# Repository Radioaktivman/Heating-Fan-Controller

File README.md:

# Heating Fan Controller

A temperature-controlled fan system for improving radiator efficiency through forced convection.

## Overview

This project provides an automated control system for heating radiator fans. By using forced convection, it significantly improves the heat output and efficiency of traditional radiators, especially at lower flow temperatures. This is particularly beneficial for heat pump systems that operate more efficiently at lower temperatures.

## Features

- **Temperature-Based Control**: Automatically activates fans based on radiator temperature
- **PWM Fan Control**: Smooth and quiet fan speed regulation
- **Efficient Heat Distribution**: Improves radiator efficiency and room heating
- **Low Noise Operation**: Designed for quiet residential use

## Why Use Radiator Fans?

Classical radiators typically require high flow temperatures to effectively heat a room. Adding forced convection with PC fans can:

- Significantly enhance radiator efficiency at low flow temperatures
- Enable heat pumps to operate at optimal (lower) temperatures
- Reduce heating costs while maintaining comfort
- Improve heat distribution in the room

### Advanced Monitoring and Control

With four temperature sensors, this controller provides comprehensive monitoring of the entire heating cycle:

- **Flow/Return Temperature Monitoring**: Track the temperature difference across the radiator to measure heat transfer efficiency
- **Air Temperature Delta**: Measure the temperature increase from inlet (bottom) to outlet (top) to quantify the actual heating effect
- **Performance Optimization**: Automatically adjust fan speed based on the temperature differentials to maximize efficiency
- **System Diagnostics**: Identify issues like poor circulation, air locks, or insufficient flow temperatures
- **Energy Efficiency**: Calculate the actual heat output and optimize fan operation to minimize electricity consumption while maximizing heat distribution

## Hardware Components

### Required Components
- **ESP Heating Controller PCB** (Rev 1.0 - design files in `/PCB` folder)
  - PCBs available from maintainer (contact via PM)
  - [3D-printable housing available on Thingiverse](https://www.thingiverse.com/thing:7254499)
- Temperature sensors: DS18B20 (up to 4 sensors supported)
- **12V PC fans** - Both 3-pin and 4-pin fans  up to 6 fans total
  - 3-pin fans: Standard DC voltage control
  - 4-pin PWM fans: Precise PWM speed control (recommended for quieter operation)
  - Note: All fans operate at the same speed (shared PWM signal)
- 12V power supply 
- **[3D-printed mounting clips](https://www.thingiverse.com/thing:5943925)** for attaching fans to radiators 

### Recommended Fans
High-quality PC fans operating at low speeds (<500 RPM) are essentially inaudible while providing significant heat output improvement. The controller supports both 3-pin and 4-pin fans.

## PCB Design

*ESP Heating Controller Rev 1.0 by 2SimpleEnergy GmbH*

The `/PCB` folder contains the custom PCB design files for this project. 

### Hardware Specifications

**Microcontroller:**
- ESP32-WROOM module (WiFi/Bluetooth enabled)
- Enables smart home integration and remote monitoring

**Fan Outputs:**
- **6 fan output channels** (F1-F6)
- **All channels share the same PWM control signal** - fans operate synchronously at the same speed
- Supports multiple fans or fan groups connected across the 6 outputs
- **Compatible with both 3-pin and 4-pin PC fans:**
  - **3-pin fans**: Standard DC voltage control (full voltage = full speed)
  - **4-pin PWM fans**: Advanced PWM control with tachometer feedback for precise speed regulation and RPM monitoring
- Standard 4-pin fan connectors for easy plug-and-play installation

**Temperature Sensor Inputs:**
- **3 Pin Connector ** (S1-S4) for DS18B20 or similar sensors
- Designed for comprehensive heating system monitoring:
  - **Flow temperature**: Monitor water entering the radiator
  - **Return flow temperature**: Monitor water leaving the radiator
  - **Air inlet temperature**: Measure air temperature at bottom of radiator (before heating)
  - **Air outlet temperature**: Measure air temperature at top of radiator (after heating)
- Pull-up resistors (R1, R3, R5, R7) integrated on board
- Enables precise control based on actual radiator performance and efficiency calculations

**User Interface:**
- 3 tactile buttons (SW1, SW2, SW3) for manual control and configuration
- Status LED indicators

**Power Supply:**
- DC barrel jack connector (DC0) for 12V input
- Onboard voltage regulation for ESP32 (3.3V)

**PCB Housing:**
A 3D-printable housing for this PCB is available on Thingiverse for protection and professional mounting:
👉 **[ESP Heating Controller PCB Housing](https://www.thingiverse.com/thing:7254499)**

**PCB Availability:**
I have some leftover PCBs ! If you're interested in procuring a board instead of manufacturing it yourself, please contact me via private message on GitHub.

## Installation

### Hardware Setup

1. **3D-print the components**:
   - Download and print the **[PCB housing](https://www.thingiverse.com/thing:7254499)** for the controller
   - Download and print the **[fan mounting clips](https://www.thingiverse.com/thing:5943925)** (2 clips per fan)
2. **Assemble the controller**:
   - Install the ESP Heating Controller PCB into the housing
   - Mount the housing to wall or heating
3. **Prepare the fans**: Mount the PC fans using the printed clips below your radiators
   - Insert clips from below between the radiator ribs
   - Ensure secure fit (designed for 75mm inner distance, adjustable)
   - Use cable ties through the eyelets for cable management
3. **Wire the temperature sensor**: Connect DS18B20 to the controller
   - Red: +3.3V 
   - Yellow/Data: Data line (with 4.7kΩ pull-up resistor)
   - Black: GND
3. **Connect the fans**: Wire fans to the controller output
4. **Power supply**: Connect 12V power supply

### Software Setup

1. Clone this repository:
```bash
git clone https://github.com/Radioaktivman/Heating-Fan-Controller.git
cd Heating-Fan-Controller
```

2. **Firmware Option: Tasmota**

This controller uses Tasmota firmware for easy configuration and smart home integration.

**Step-by-Step Tasmota Configuration:**

**Step 1: Flash Tasmota Firmware**
1. Flash Tasmota firmware to the ESP32 module using your preferred method (web flasher, esptool, etc.)
2. Select ESP32 variant during flashing

**Step 2: Initial WiFi Setup**
1. Power on the device - it will create a WiFi access point named "tasmota-XXXXXX"
2. Connect to this access point with your phone/computer
3. Configure your WiFi credentials:
   - SSID: YourNetworkName
   - Password: [Your WiFi Password]
4. The device will restart and connect to your network

**Step 3: Access Tasmota Web Interface**
1. Find the device's IP address (check your router or use Tasmota discovery)
2. Open a web browser and navigate to the IP address
3. You should see the Tasmota web interface

**Step 4: Configure Module Type**
1. Go to **Configuration** → **Configure Module**
2. Set **Module type** to **ESP32S3 (1)**
3. Click **Save** - the device will restart

**Step 5: Configure GPIO Pins**
After restart, go back to **Configuration** → **Configure Module** and set the following GPIO pins:

| GPIO Pin | Function | Number |
|----------|----------|--------|
| GPIO03 | DS18x20 | 4 |
| GPIO04 | Button | 1 |
| GPIO05 | Button | 2 |
| GPIO06 | Button | 3 |
| GPIO11 | DS18x20 | 3 |
| GPIO14 | DS18x20 | 2 |
| GPIO16 | Relay_i | 1 |
| GPIO18 | PWM | 1 |
| GPIO48 | DS18x20 | 1 |

Leave all other GPIO pins set to **None**.

Click **Save** - the device will restart again.

**Step 6: Configure Temperature Sensor Names**
1. Go to **Console**
2. Enter the following commands to name your DS18B20 sensors:
```
Backlog DS18Alias 1,Flow; DS18Alias 2,Return; DS18Alias 3,AirIn; DS18Alias 4,AirOut
```

**Step 7: Configure Control Rules**
The three buttons provide manual control for the fan system. Configure the automation rules:

1. Go to **Console**
2. Enable Rule1:
```
Rule1 1
```
3. Configure Rule1 with the following logic:
```
Rule1 
ON Button3#state DO Dimmer + ENDON 
ON Button2#state DO Dimmer - ENDON 
ON Button1#state DO power1 toggle ENDON 
ON Dimmer#state >= 100 DO power1 off ENDON 
ON Dimmer#state < 80 DO power1 on ENDON
```

**Button Functions:**
- **Button 1 (GPIO04)**: Toggle fan power on/off
- **Button 2 (GPIO05)**: Decrease fan speed (Dimmer -)
- **Button 3 (GPIO06)**: Increase fan speed (Dimmer +)
- **Auto-control**: 
  - Fans turn OFF when dimmer reaches 100%
  - Fans turn ON when dimmer drops below 80%

**Step 8: Configure MQTT (Optional, for Home Assistant)**
1. Go to **Configuration** → **Configure MQTT**
2. Enter your MQTT broker details:
   - Host: [Your MQTT broker IP]
   - Port: 1883 (default)
   - Client: heating_controller_%06X
   - User: [Your MQTT username]
   - Password: [Your MQTT password]
   - Topic: heating_controller
3. Click **Save**

**Step 9: Test Your Setup**
1. Check that all four temperature sensors appear in the main interface
2. Test the three buttons for manual control
3. Verify PWM control is working by adjusting the dimmer
4. Monitor MQTT messages if configured

Your ESP Heating Controller is now fully configured and ready to use!

## Contributing

Contributions are welcome! Please feel free to submit a Pull Request or open an Issue for bugs, suggestions, or improvements.

## License

This project is licensed under the MIT License - see the [LICENSE](LICENSE) file for details.

## Acknowledgments

Inspired by similar projects in the home automation community focused on improving heating efficiency and reducing energy costs.

## Roadmap / TODO

### Upcoming Features

- **Thermostat Control Unit**: A thermostat control module will be added in the next update to gain full control of the heating system. This will enable:
  - Complete closed-loop heating control
  - Automatic heating system regulation based on flor and/or air temperature
  - Enhanced energy efficiency through intelligent heating management

## Contact

Project maintained by [@Radioaktivman](https://github.com/Radioaktivman)

---

**Note**: This is an early-stage project. Documentation and features will be expanded as development continues.

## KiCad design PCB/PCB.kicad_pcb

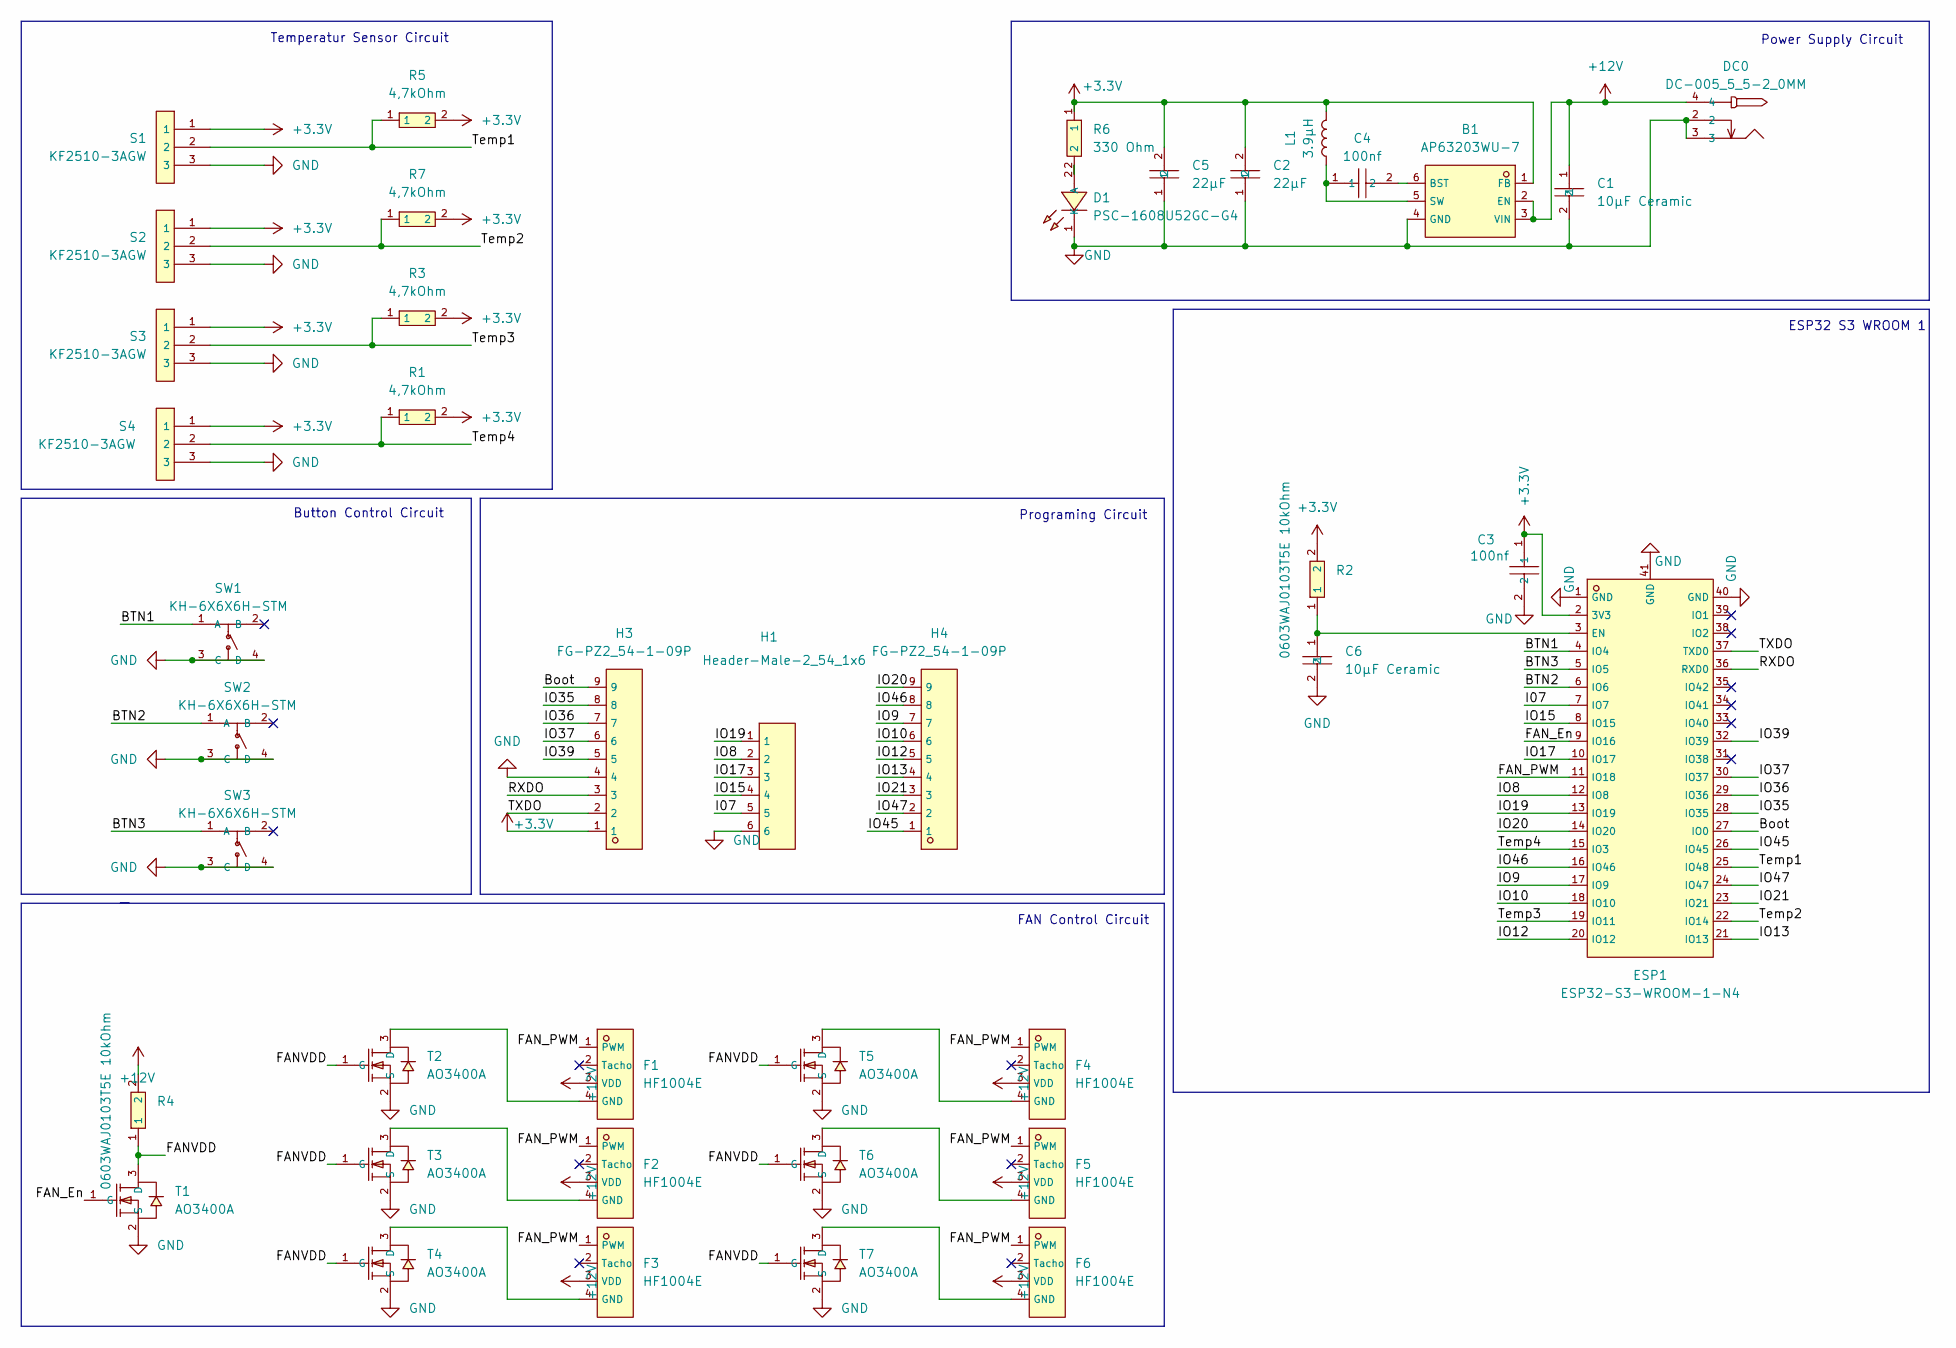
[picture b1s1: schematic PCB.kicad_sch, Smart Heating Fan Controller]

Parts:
B1: AP63203WU-7; TSOT-26_L2.9-W1.6-P0.95-LS2.8-BL; LCSC C780769
C1, C6: 10µF Ceramic; C1206; LCSC C13585
C2, C5: 22µF; C1206; LCSC C12891
C3, C4: 100nf; C0603; LCSC C1591
D1: PSC-1608U52GC-G4; LED0603-RD_GREEN; LCSC C22371297
DC0: DC-005_5_5-2_0MM; DC-IN-TH_DC-5520-1; LCSC C16214
ESP1: ESP32-S3-WROOM-1-N4; WIFIM-SMD_ESP32-S3-WROOM-1-N8; LCSC C2913197
F1, F2, F3, F4, F5, F6: HF1004E; CONN-TH_4P-P2.54_HF1004E; LCSC C2761402
H1: Header-Male-2_54_1x6; HDR-TH_6P-P2.54-V-M-1; LCSC C37208
H3, H4: FG-PZ2_54-1-09P; HDR-TH_9P-P2.54-V-M; LCSC C25687201
L1: 3.9µH; IND-SMD_L4.0-W4.0; LCSC C96899
R1, R3, R5, R7: 4,7kOhm; R0805; LCSC C17673
R2, R4: 0603WAJ0103T5E 10kOhm; R0603; LCSC C15401
R6: 330 Ohm; R1206; LCSC C25374
S1, S2, S3, S4: KF2510-3AGW; CONN-TH_KF2510-3AGW; LCSC C68663
SW1, SW2, SW3: KH-6X6X6H-STM; SW-SMD_4P-L6.0-W6.0-P4.50-LS9.0-3; LCSC C2837532
T1, T2, T3, T4, T5, T6, T7: AO3400A; SOT-23-3_L2.9-W1.3-P1.90-LS2.4-BR; LCSC C20917

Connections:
+3.3V: B1.1 (FB), C2.2, C3.1, C5.2, ESP1.2 (3V3), H3.1, L1.2, R1.2, R2.2, R3.2, R5.2, R6.1, R7.2, S1.1, S2.1, S3.1, S4.1
+12V: B1.2 (EN), B1.3 (VIN), C1.1, DC0.4, F1.3 (VDD), F2.3 (VDD), F3.3 (VDD), F4.3 (VDD), F5.3 (VDD), F6.3 (VDD), R4.2
/BTN1: ESP1.4 (IO4), SW1.1 (A)
/BTN2: ESP1.6 (IO6), SW2.1 (A)
/BTN3: ESP1.5 (IO5), SW3.1 (A)
/Boot: ESP1.27 (IO0), H3.9
/FANVDD: R4.1, T1.3 (D), T2.1 (G), T3.1 (G), T4.1 (G), T5.1 (G), T6.1 (G), T7.1 (G)
/FAN_En: ESP1.9 (IO16), T1.1 (G)
/FAN_PWM: ESP1.11 (IO18), F1.1 (PWM), F2.1 (PWM), F3.1 (PWM), F4.1 (PWM), F5.1 (PWM), F6.1 (PWM)
/I07: ESP1.7 (IO7), H1.5
/IO8: ESP1.12 (IO8), H1.2
/IO9: ESP1.17 (IO9), H4.7
/IO10: ESP1.18 (IO10), H4.6
/IO12: ESP1.20 (IO12), H4.5
/IO13: ESP1.21 (IO13), H4.4
/IO15: ESP1.8 (IO15), H1.4
/IO17: ESP1.10 (IO17), H1.3
/IO19: ESP1.13 (IO19), H1.1
/IO20: ESP1.14 (IO20), H4.9
/IO21: ESP1.23 (IO21), H4.3
/IO35: ESP1.28 (IO35), H3.8
/IO36: ESP1.29 (IO36), H3.7
/IO37: ESP1.30 (IO37), H3.6
/IO39: ESP1.32 (IO39), H3.5
/IO45: ESP1.26 (IO45), H4.1
/IO46: ESP1.16 (IO46), H4.8
/IO47: ESP1.24 (IO47), H4.2
/RXDO: ESP1.36 (RXD0), H3.3
/TXDO: ESP1.37 (TXD0), H3.2
/Temp1: ESP1.25 (IO48), R5.1, S1.2
/Temp2: ESP1.22 (IO14), R7.1, S2.2
/Temp3: ESP1.19 (IO11), R3.1, S3.2
/Temp4: ESP1.15 (IO3), R1.1, S4.2
GND: B1.4 (GND), C1.2, C2.1, C3.2, C5.1, C6.2, D1.1 (K), DC0.2, DC0.3, ESP1.1 (GND), ESP1.40 (GND), ESP1.41 (GND), H1.6, H3.4, S1.3, S2.3, S3.3, S4.3, SW1.3 (C), SW1.4 (D), SW2.3 (C), SW2.4 (D), SW3.3 (C), SW3.4 (D), T1.2 (S), T2.2 (S), T3.2 (S), T4.2 (S), T5.2 (S), T6.2 (S), T7.2 (S)
unnamed: B1.6 (BST), C4.2
unnamed: B1.5 (SW), C4.1, L1.1
unnamed: D1.2 (A), R6.2
unnamed: C6.1, ESP1.3 (EN), R2.1
unnamed: F1.4 (GND), T2.3 (D)
unnamed: F2.4 (GND), T3.3 (D)
unnamed: F3.4 (GND), T4.3 (D)
unnamed: F4.4 (GND), T5.3 (D)
unnamed: F5.4 (GND), T6.3 (D)
unnamed: F6.4 (GND), T7.3 (D)

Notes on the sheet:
Programing Circuit
Power Supply Circuit
Temperatur Sensor Circuit
ESP32 S3 WROOM 1
FAN Control Circuit
Button Control Circuit

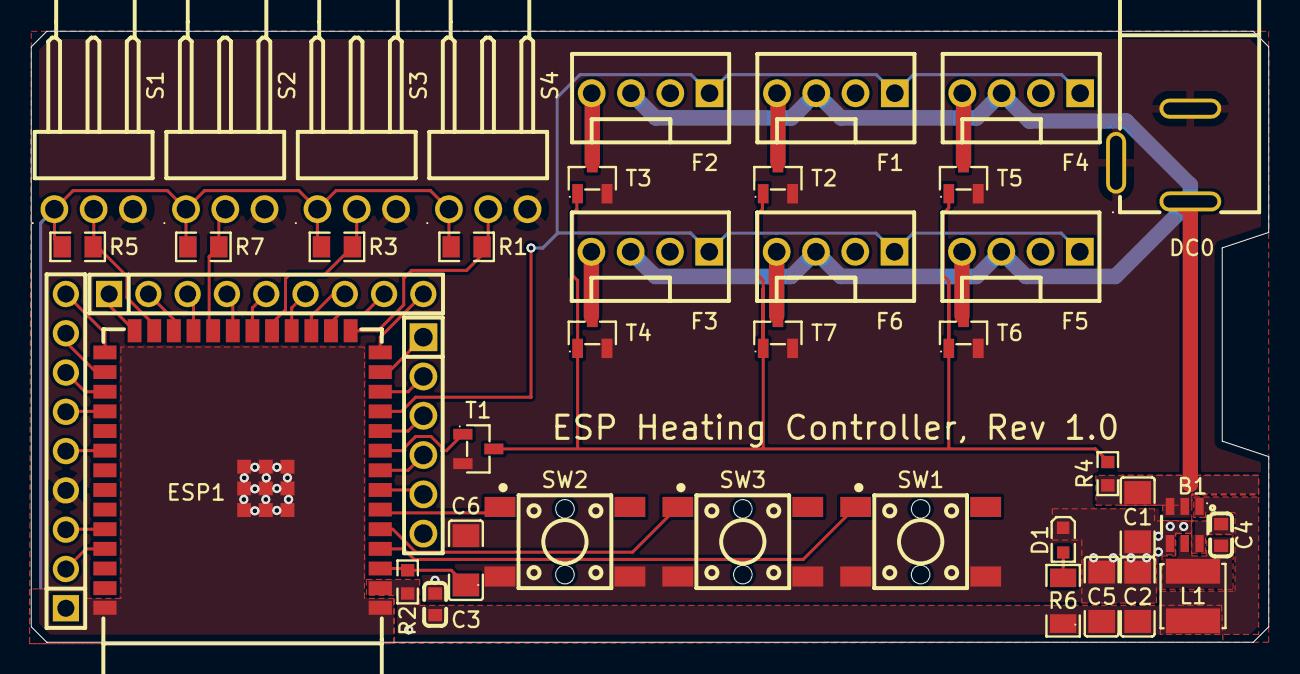
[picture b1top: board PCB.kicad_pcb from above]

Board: 2 copper layers, 80.0 x 39.5 mm, 41 parts (0 on the bottom side), 44 nets.

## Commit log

2025-12-29 Uploaded Project Files
2025-12-29 expanded readme
2025-12-29 fix image path
2025-12-29 added reference to housing thing on thingiverse
2025-12-29 fixed todos
2026-01-01 Removed Company Name
